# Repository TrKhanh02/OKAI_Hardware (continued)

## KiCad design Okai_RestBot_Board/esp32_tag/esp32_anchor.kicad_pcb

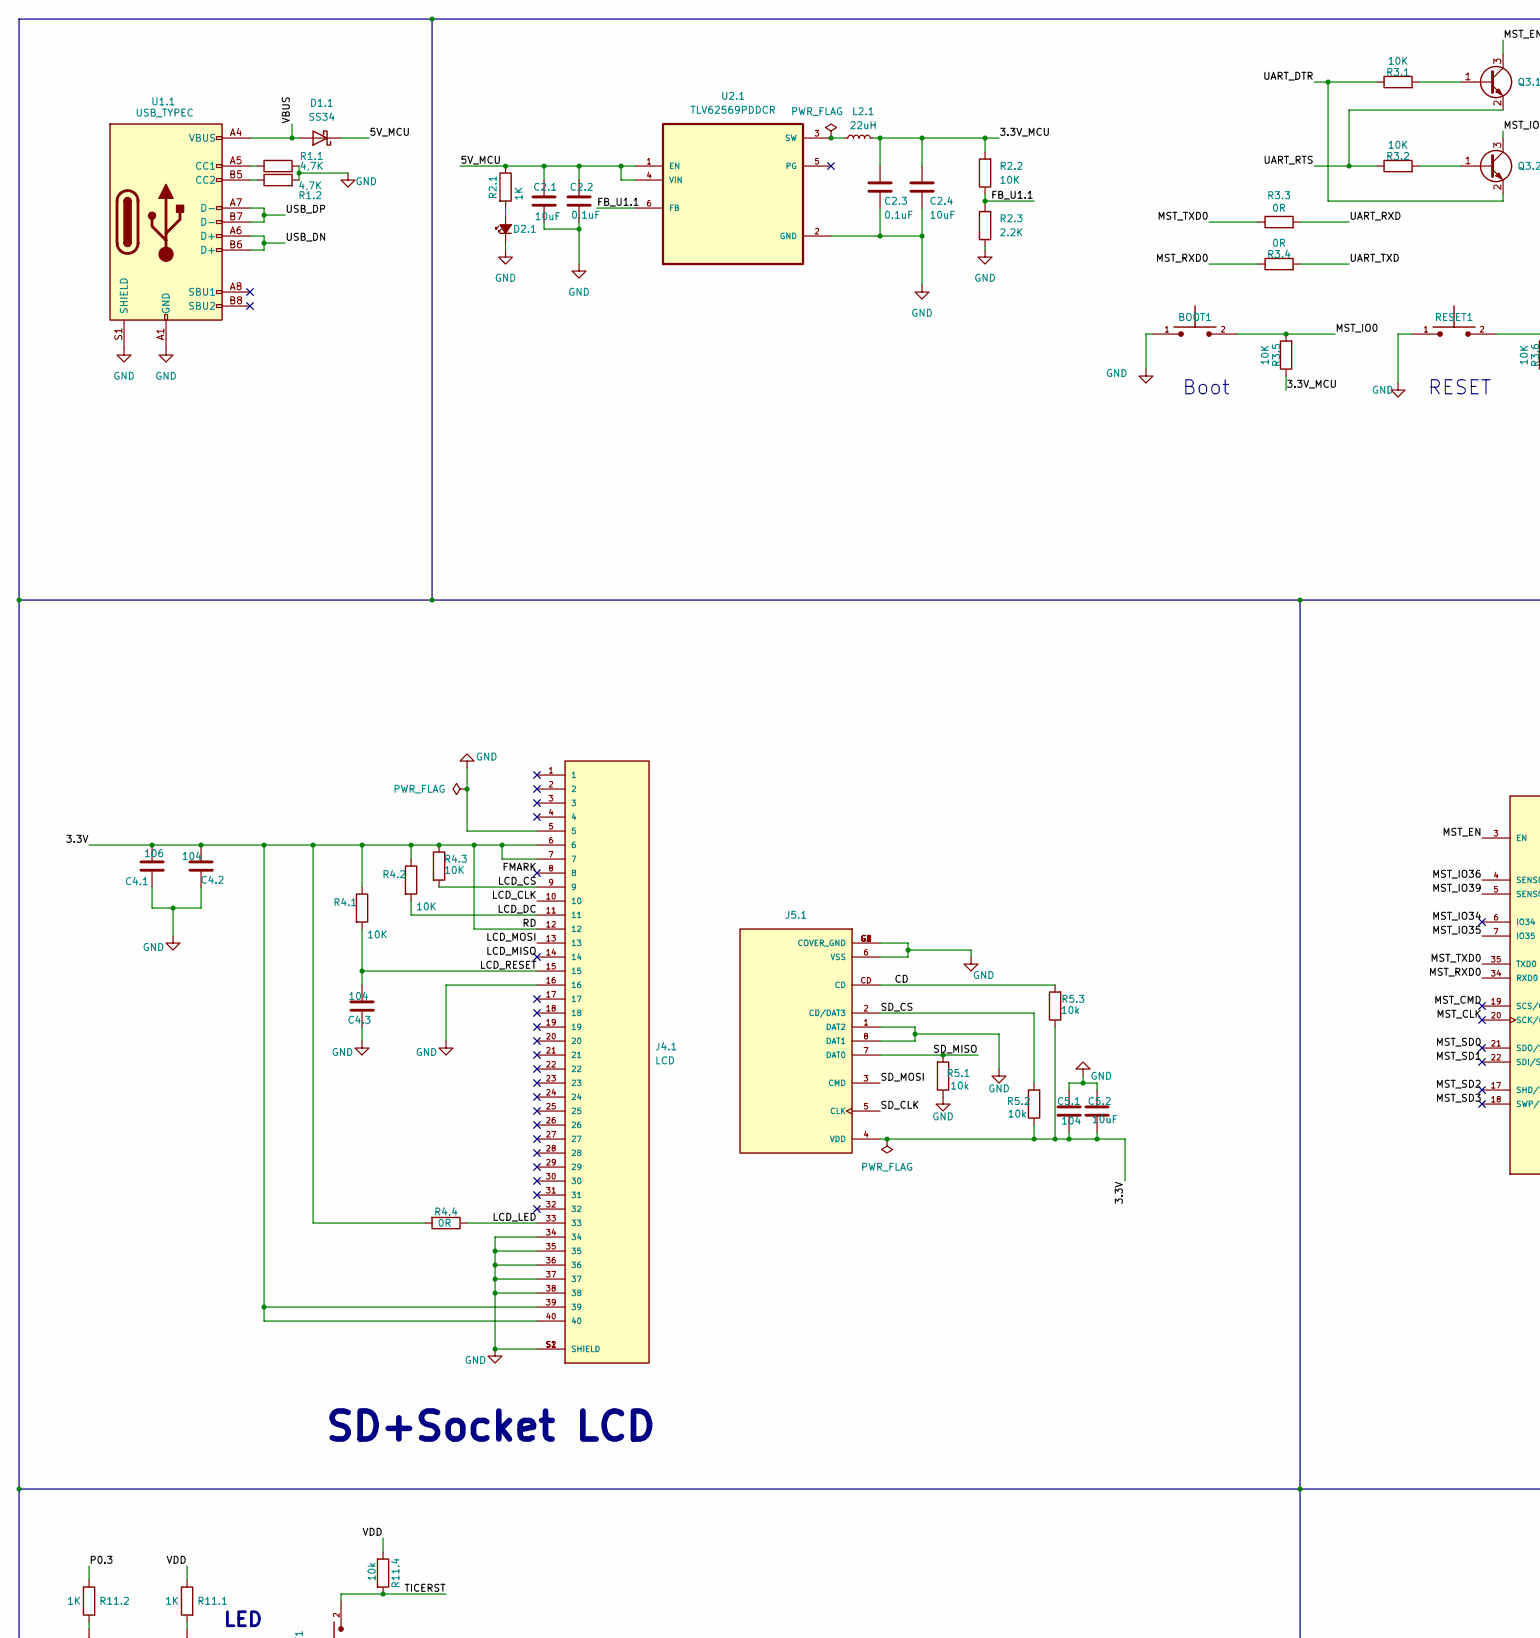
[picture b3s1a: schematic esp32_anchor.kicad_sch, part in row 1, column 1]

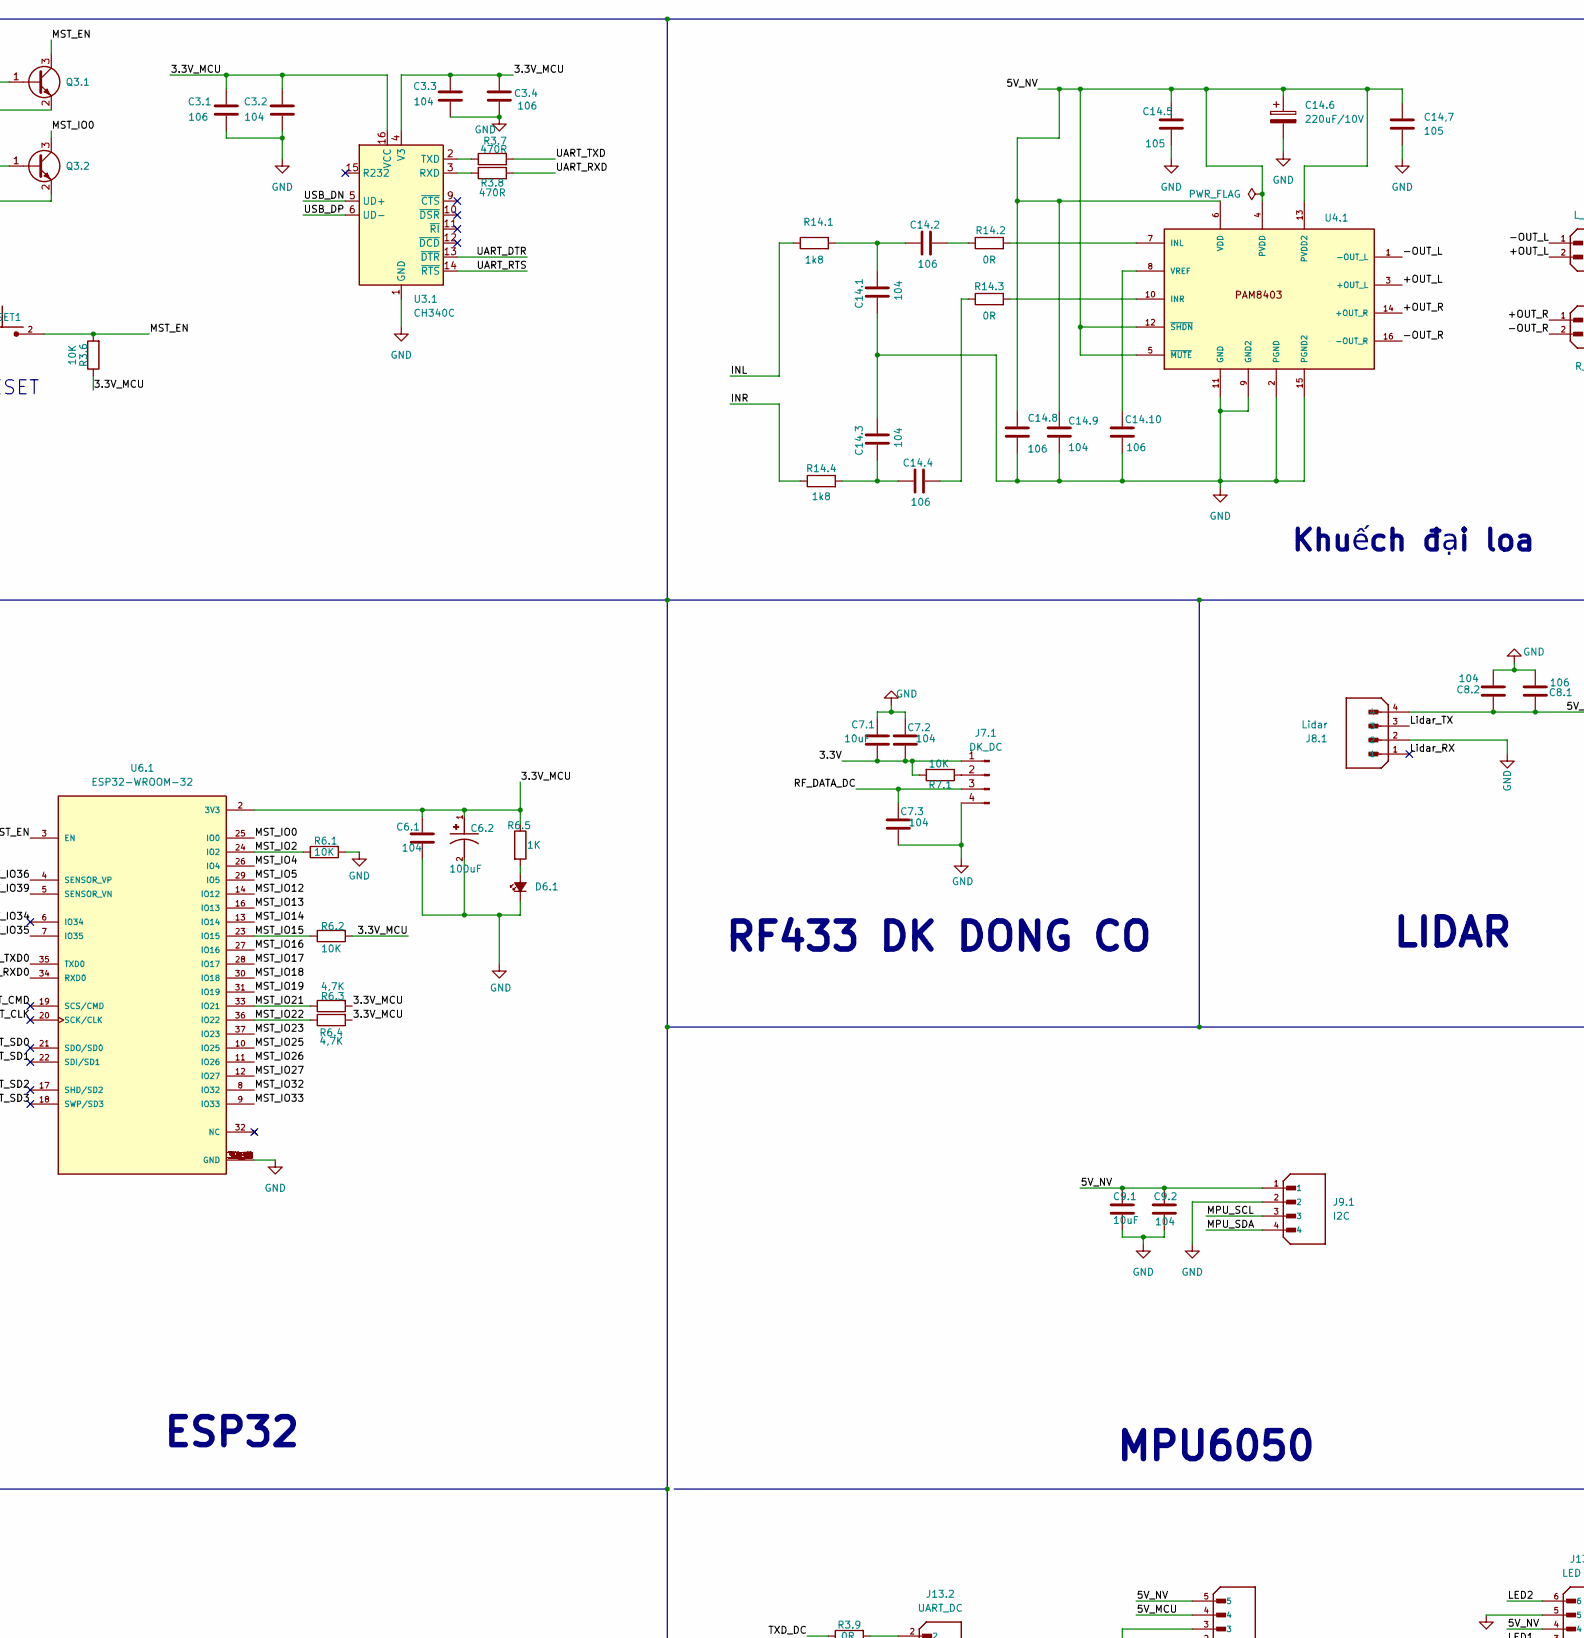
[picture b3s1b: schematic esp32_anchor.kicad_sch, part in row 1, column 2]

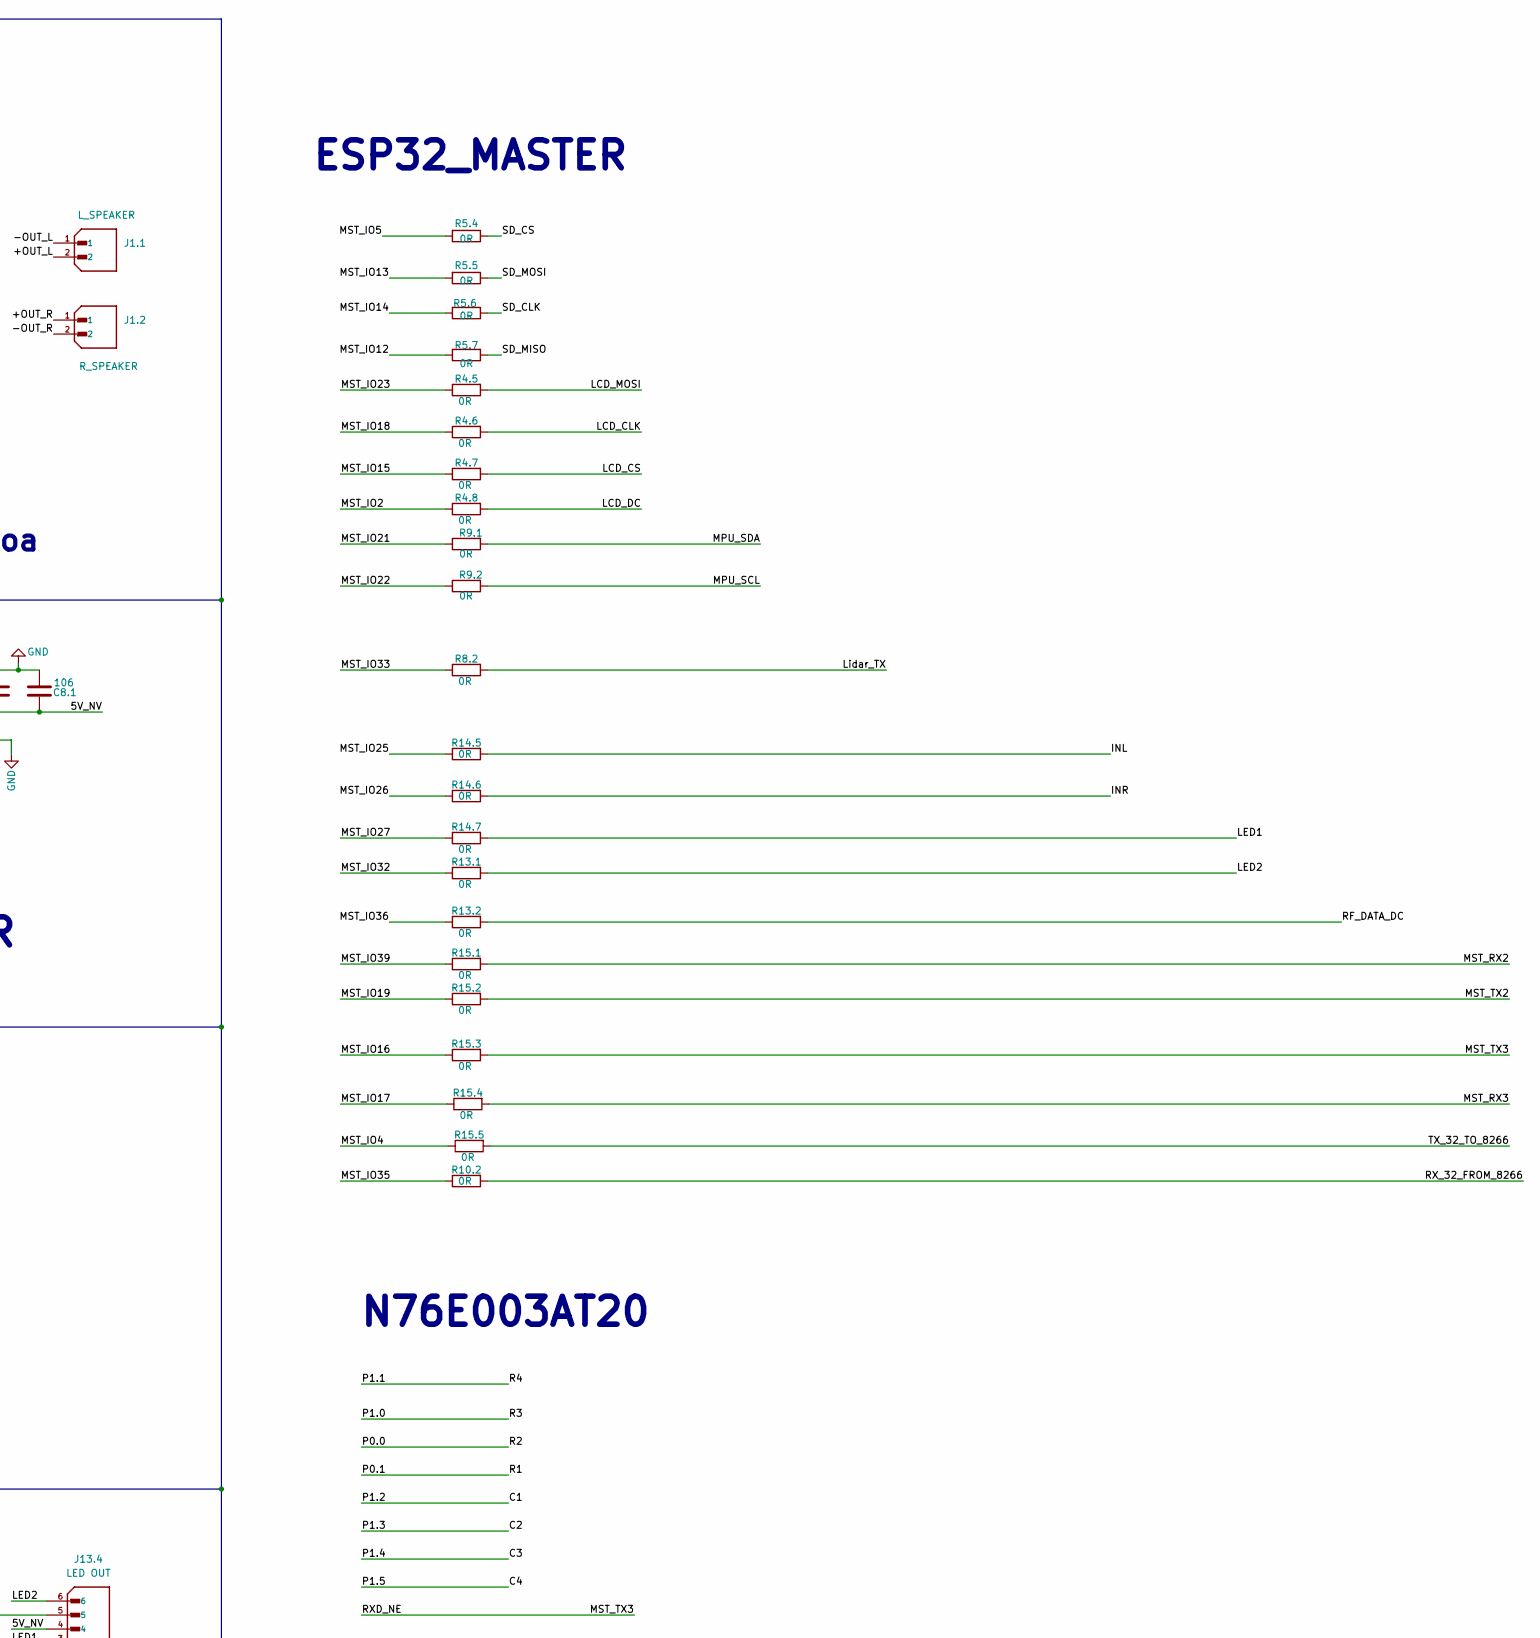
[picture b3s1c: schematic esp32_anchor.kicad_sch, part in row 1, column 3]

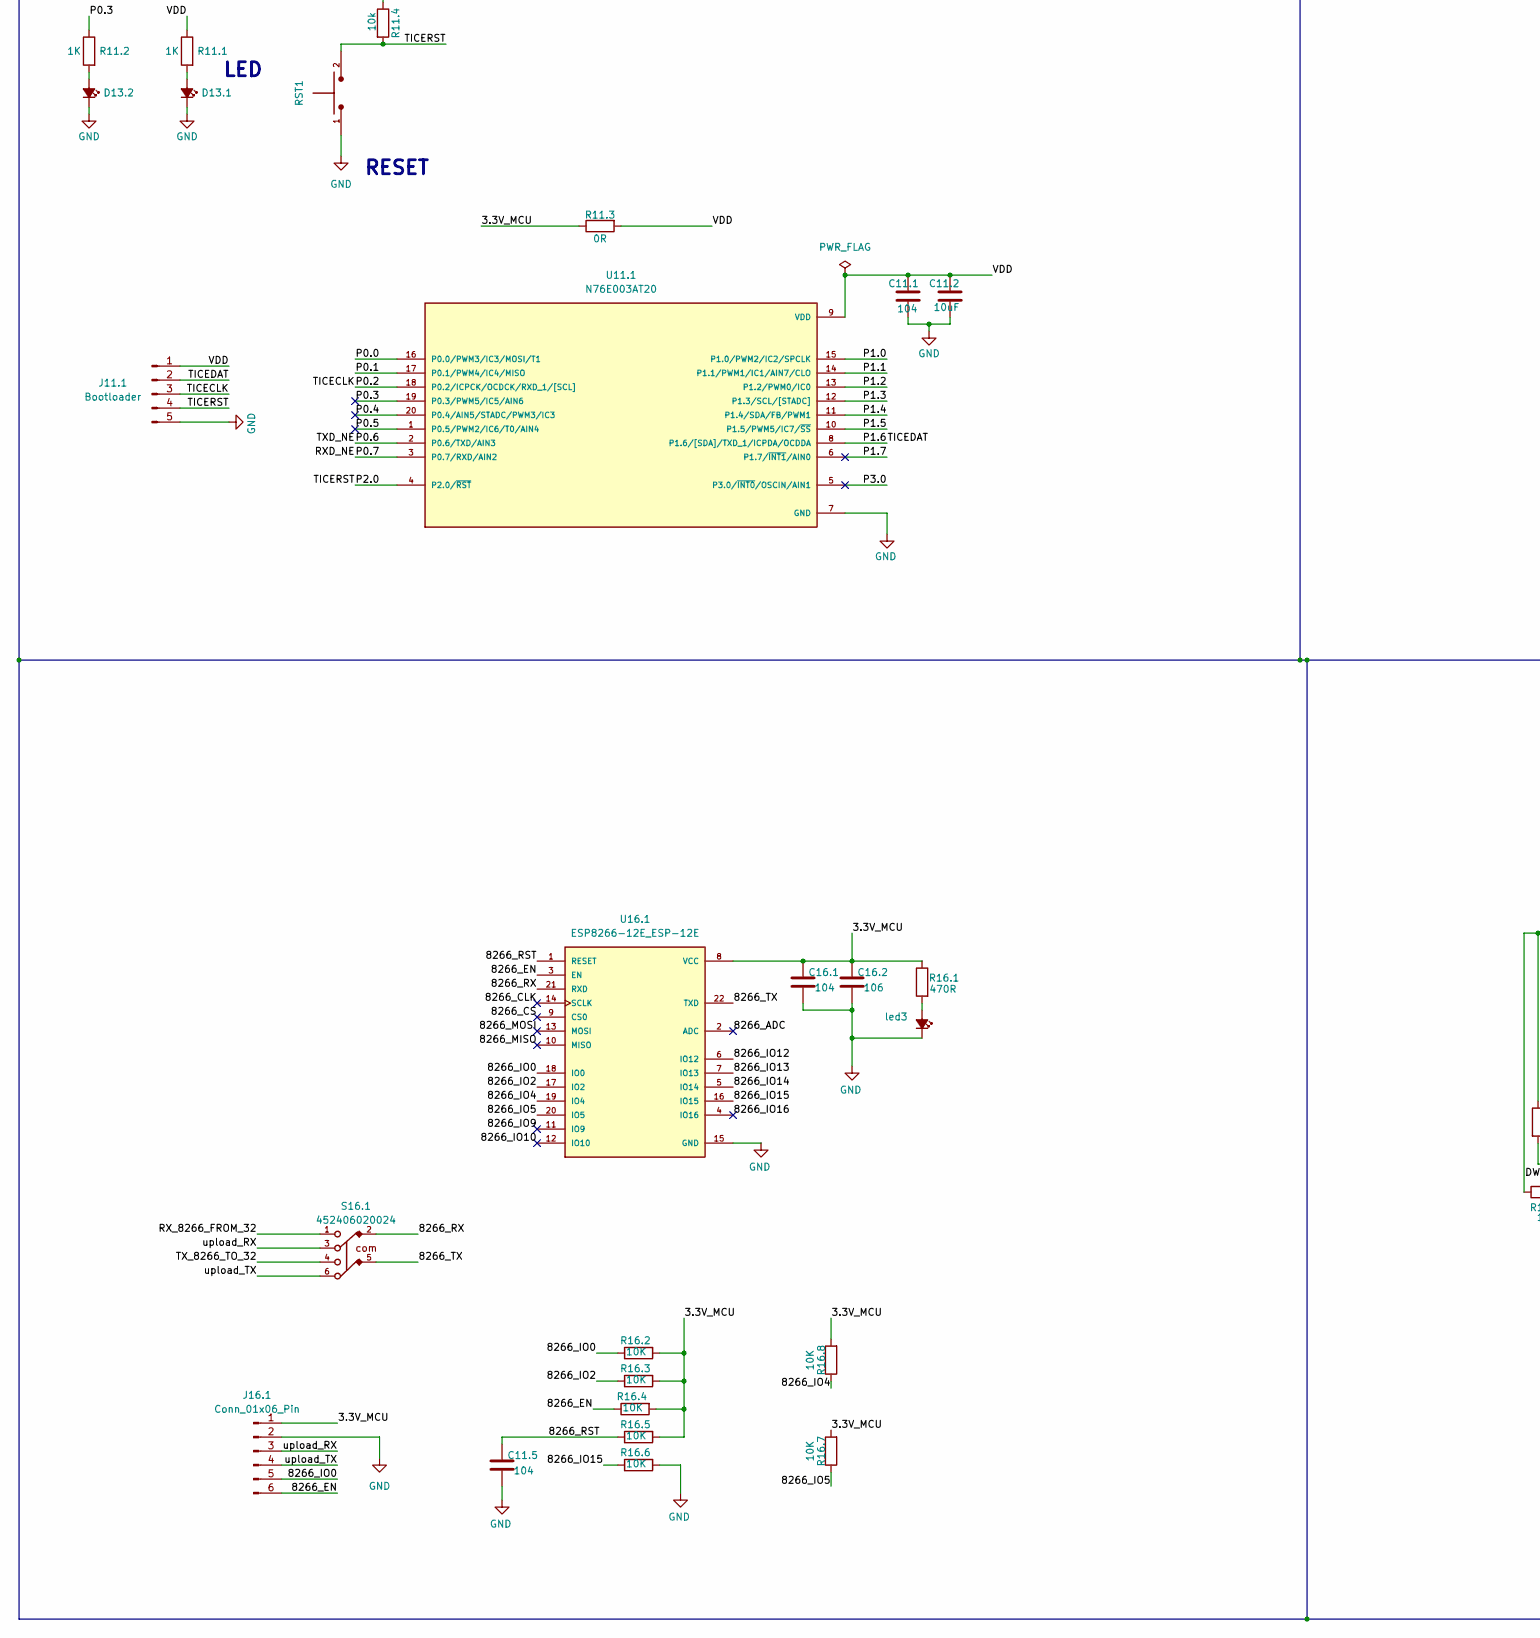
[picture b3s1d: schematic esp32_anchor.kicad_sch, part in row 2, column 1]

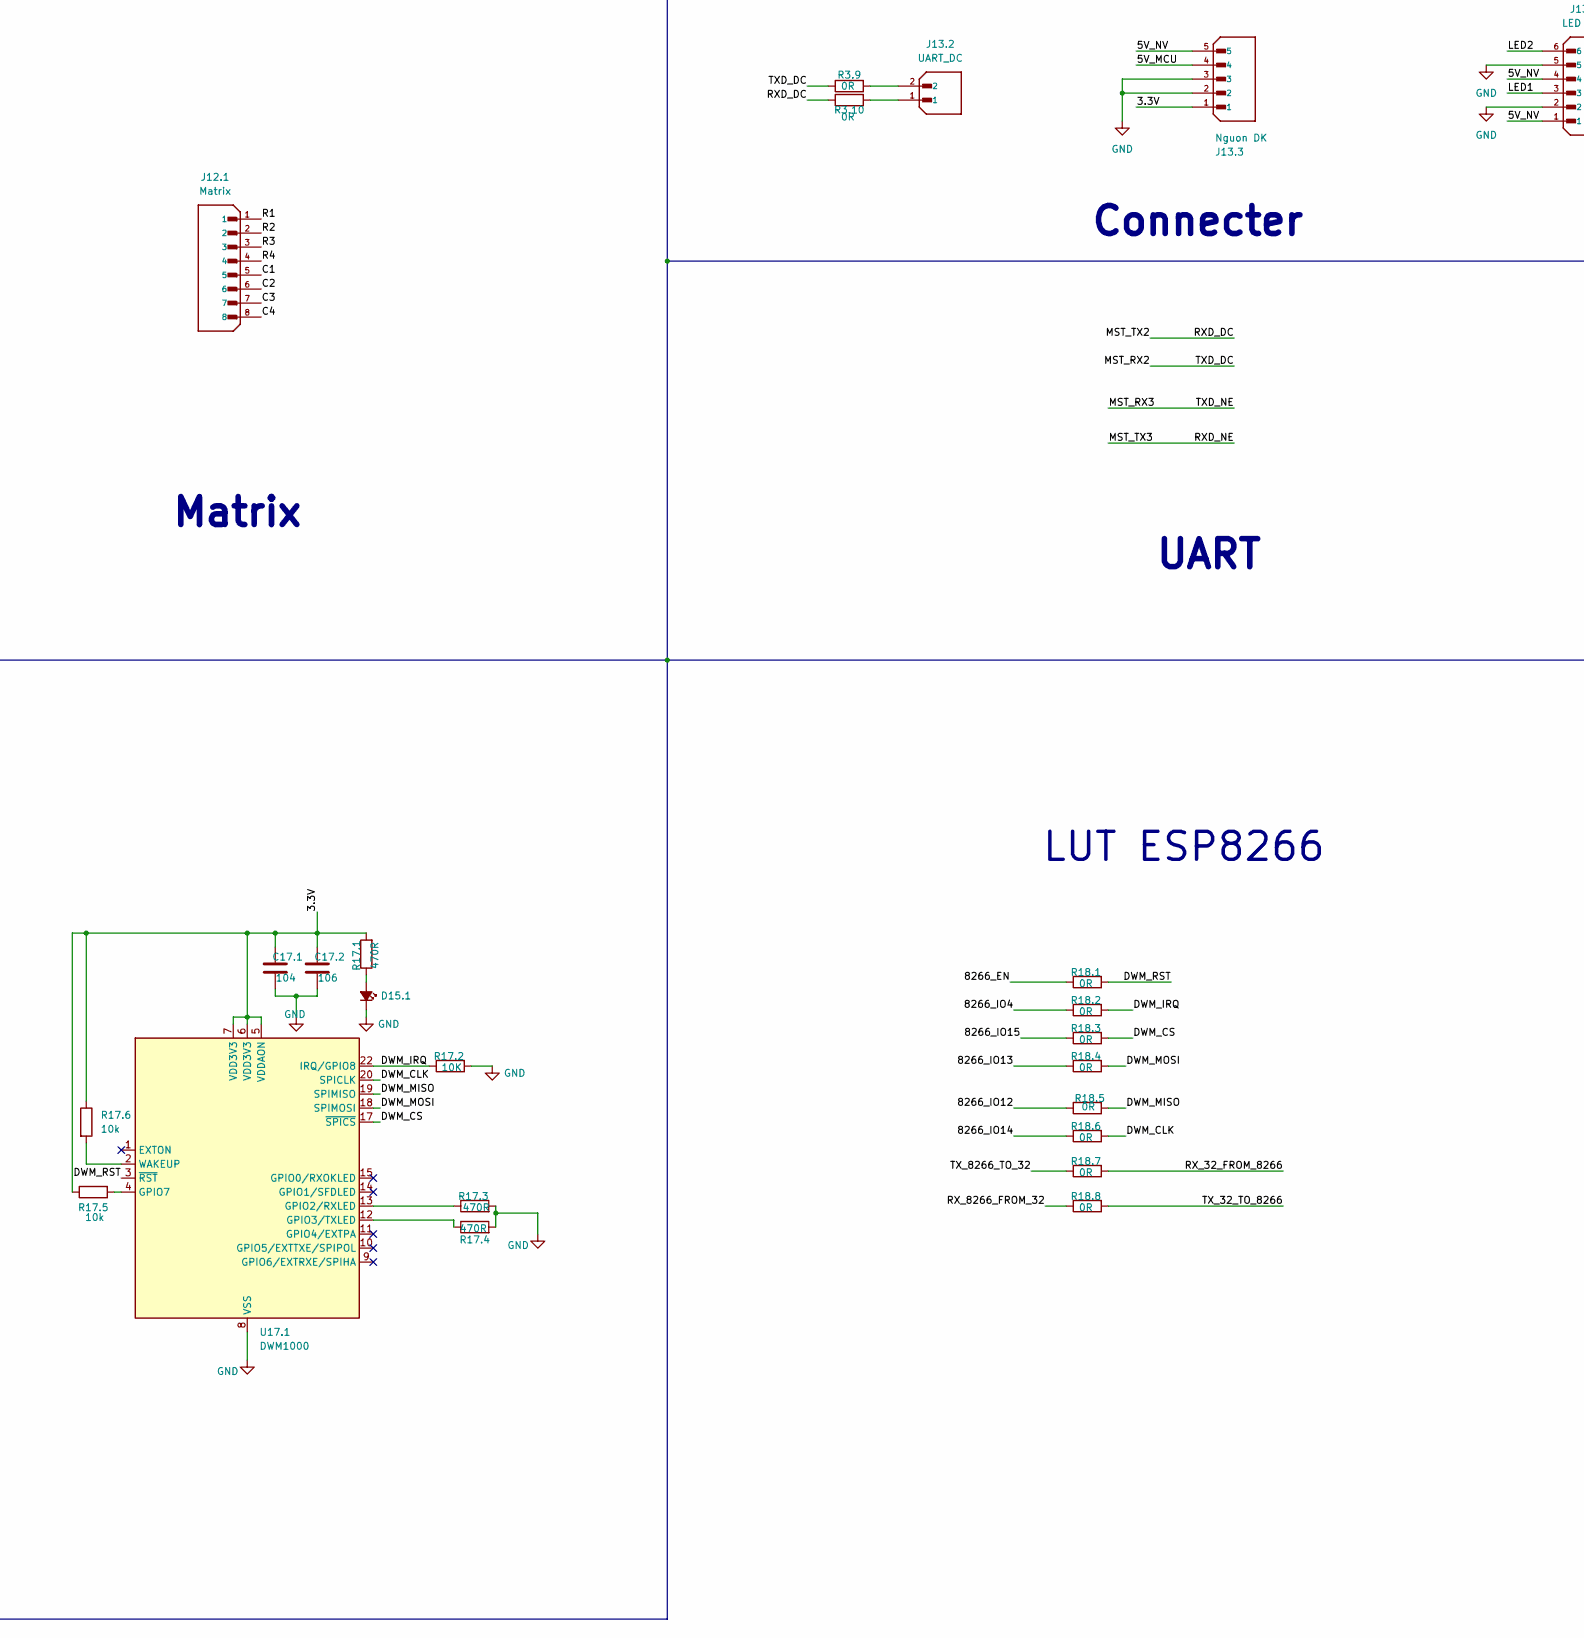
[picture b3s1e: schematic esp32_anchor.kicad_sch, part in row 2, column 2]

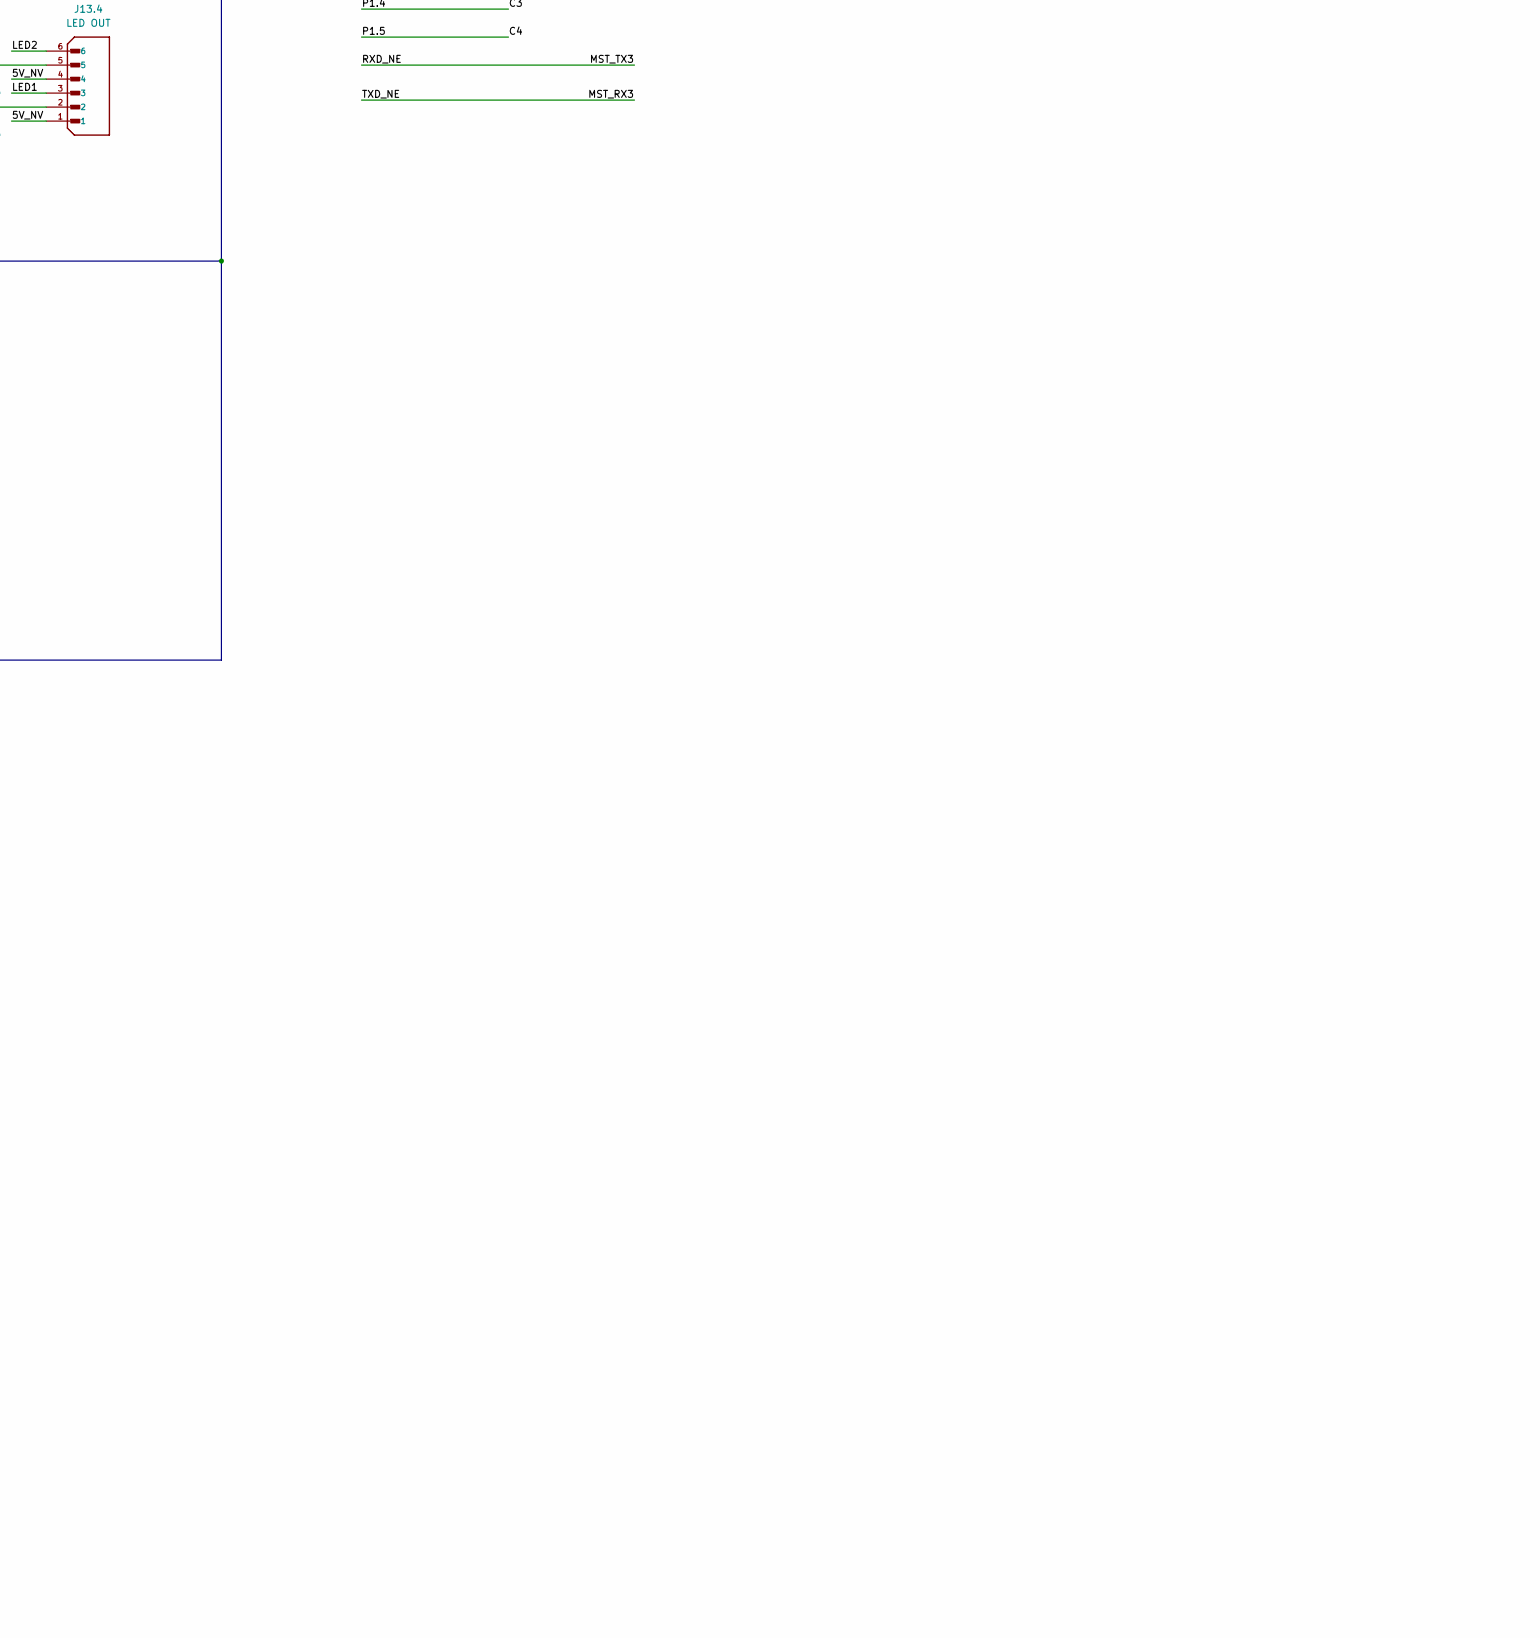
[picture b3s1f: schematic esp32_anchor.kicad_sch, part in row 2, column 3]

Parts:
BOOT1: TS10-63-26-BE-250-SMT-TR; SW_TS10-63-26-BE-250-SMT-TR; PARTREV 1.0
C2.1, C2.4: 10uF; C_0805_2012Metric
C2.2, C2.3: 0.1uF; C_0805_2012Metric
C3.1, C3.4, C4.1, C8.1, C16.2, C17.2: 106; C_0805_2012Metric_Pad1.18x1.45mm_HandSolder
C3.2, C3.3, C4.2, C4.3, C5.1, C6.1, C7.2, C7.3, C8.2, C9.2, C11.1, C11.5, C16.1, C17.1: 104; C_0805_2012Metric_Pad1.18x1.45mm_HandSolder
C5.2, C7.1, C9.1, C11.2: 10uF; C_0805_2012Metric_Pad1.18x1.45mm_HandSolder
C6.2: 100uF; CAPMP3216X180N; PARTREV 031320
C14,7, C14.5: 105; C_0805_2012Metric
C14.1, C14.3, C14.9: 104; C_0805_2012Metric
C14.2, C14.4, C14.8, C14.10: 106; C_0805_2012Metric
C14.6: 220uF/10V; CP_Elec_6.3x5.4
D1.1: SS34; D_SMA
D2.1, D6.1, D13.1, D13.2, D15.1: LED_Small_Filled; LED_0805_2012Metric_Pad1.15x1.40mm_HandSolder
J1.1: L_SPEAKER; JST_B2B-XH-A; PARTREV N/A
J1.2: R_SPEAKER; JST_B2B-XH-A; PARTREV N/A
J4.1: LCD; TE_4-1734592-0; PARTREV C
J5.1: SD; CUI_MSD-1-A; PARTREV 1.0
J7.1: DK_DC; PinSocket_1x04_P2.54mm_Vertical
J8.1: Lidar; HRS_DF14-4P-1.25H_22_
J9.1: I2C; JST_B4B-XH-A_LF__SN_; PARTREV 7/4/21
J11.1: Bootloader; PinHeader_1x05_P2.54mm_Vertical
J12.1: Matrix; JST_B8B-XH-A_LF__SN_; PARTREV 7/4/21
J13.2: UART_DC; JST_B2B-XH-A_LF__SN_; PARTREV N/A
J13.3: Nguon DK; JST_B5B-XH-A; PARTREV 7/4/21
J13.4: LED OUT; JST_B6B-XH-A_LF__SN_; PARTREV 7/4/21
J16.1: Conn_01x06_Pin; PinSocket_1x06_P2.54mm_Vertical
L2.1: 22uH; L_Ferrocore_DLG-0705
Q3.1, Q3.2: SS8050; SOT-23
R1.1, R1.2, R6.3, R6.4: 4,7K; R_0805_2012Metric_Pad1.20x1.40mm_HandSolder
R2.1, R6.5, R11.1, R11.2: 1K; R_0805_2012Metric_Pad1.20x1.40mm_HandSolder
R2.2: 10K; R_0805_2012Metric
R2.3: 2.2K; R_0805_2012Metric
R3.1, R3.2, R3.5, R3.6, R4.1, R4.2, R4.3, R6.1, R6.2, R7.1, R16.2, R16.3, R16.4, R16.5, R16.6, R16.7, R16.8, R17.2: 10K; R_0805_2012Metric_Pad1.20x1.40mm_HandSolder
R3.3, R3.4, R3.9, R3.10, R4.4, R4.5, R4.6, R4.7, R4.8, R5.4, R5.5, R5.6, R5.7, R8.2, R9.1, R9.2, R10.2, R11.3, R13.1, R13.2, R14.5, R14.6, R14.7, R15.1, R15.2, R15.3, R15.4, R15.5, R18.1, R18.2, R18.3, R18.4, R18.5, R18.6, R18.7, R18.8: 0R; R_0805_2012Metric_Pad1.20x1.40mm_HandSolder
R3.7, R3.8, R16.1, R17.1, R17.3, R17.4: 470R; R_0805_2012Metric_Pad1.20x1.40mm_HandSolder
R5.1, R5.2, R5.3, R11.4, R17.5, R17.6: 10k; R_0805_2012Metric_Pad1.20x1.40mm_HandSolder
R14.1, R14.4: 1k8; R_0805_2012Metric
R14.2, R14.3: 0R; R_0805_2012Metric
RESET1: TS10-63-26-BE-250-SMT-TR; SW_TS10-63-26-BE-250-SMT-TR; PARTREV 1.0
RST1: TS10-63-26-BE-250-SMT-TR; SW_TS10-63-26-BE-250-SMT-TR; PARTREV 1.0
S16.1: 452406020024
U1.1: USB_TYPEC; USB_C_Receptacle_HRO_TYPE-C-31-M-12
U2.1: TLV62569PDDCR; SOT95P280X110-6N
U3.1: CH340C; SOIC-16_3.9x9.9mm_P1.27mm
U4.1: PAM8403; SOP-16
U6.1: ESP32-WROOM-32; MODULE_ESP32-WROOM-32
U11.1: N76E003AT20; SOP65P640X120-20N; PARTREV 1.04
U16.1: ESP8266-12E_ESP-12E; XCVR_ESP8266-12E_ESP-12E
U17.1: DWM1000
led3: LED_Small_Filled; LED_0805_2012Metric_Pad1.15x1.40mm_HandSolder

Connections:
/3.3V: C4.1.2, C4.2.2, C5.1.1, C5.2.1, C7.1.2, C7.2.2, C17.1.1, C17.2.1, J4.1.6, J4.1.7, J4.1.12, J4.1.39, J4.1.40, J5.1.4 (VDD), J7.1.1, J13.3.1, R4.1.1, R4.2.1, R4.3.1, R4.4.2, R5.2.1, R5.3.1, R7.1.2, R17.1.2, R17.5.1, R17.6.1, U17.1.5 (VDDAON), U17.1.6 (VDD3V3), U17.1.7 (VDD3V3)
/3.3V_MCU: C2.3.1, C2.4.1, C3.1.2, C3.2.2, C3.3.2, C3.4.2, C6.1.1, C6.2.1, C16.1.1, C16.2.1, J16.1.1, L2.1.1, R2.2.2, R3.5.1, R3.6.1, R6.2.2, R6.3.2, R6.4.2, R6.5.1, R11.3.1, R16.1.1, R16.2.2, R16.3.2, R16.4.2, R16.5.2, R16.7.2, R16.8.2, U3.1.4 (V3), U3.1.16 (VCC), U6.1.2 (3V3), U16.1.8 (VCC)
/5V_MCU: C2.1.1, C2.2.1, D1.1.1 (K), J13.3.4, R2.1.1, U2.1.1 (EN), U2.1.4 (VIN)
/5V_NV: C8.1.1, C8.2.1, C9.1.1, C9.2.1, C14,7.2, C14.5.2, C14.6.1, C14.8.2, C14.9.2, J8.1.4, J9.1.1, J13.3.5, J13.4.1, J13.4.4, U4.1.4 (PVDD), U4.1.5 (~MUTE), U4.1.6 (VDD), U4.1.12 (~SHDN), U4.1.13 (PVDD2)
/8266_ADC: U16.1.2 (ADC)
/8266_CLK: U16.1.14 (SCLK)
/8266_CS: U16.1.9 (CS0)
/8266_EN: J16.1.6, R16.4.1, R18.1.1, U16.1.3 (EN)
/8266_IO0: J16.1.5, R16.2.1, U16.1.18 (IO0)
/8266_IO2: R16.3.1, U16.1.17 (IO2)
/8266_IO4: R16.8.1, R18.2.1, U16.1.19 (IO4)
/8266_IO5: R16.7.1, U16.1.20 (IO5)
/8266_IO9: U16.1.11 (IO9)
/8266_IO10: U16.1.12 (IO10)
/8266_IO12: R18.5.1, U16.1.6 (IO12)
/8266_IO13: R18.4.1, U16.1.7 (IO13)
/8266_IO14: R18.6.1, U16.1.5 (IO14)
/8266_IO15: R16.6.1, R18.3.1, U16.1.16 (IO15)
/8266_IO16: U16.1.4 (IO16)
/8266_MISO: U16.1.10 (MISO)
/8266_MOSI: U16.1.13 (MOSI)
/8266_RST: C11.5.1, R16.5.1, U16.1.1 (RESET)
/8266_RX: S16.1.2, U16.1.21 (RXD)
/8266_TX: S16.1.5, U16.1.22 (TXD)
/+OUT_L: J1.1.2, U4.1.3 (+OUT_L)
/+OUT_R: J1.2.1, U4.1.14 (+OUT_R)
/-OUT_L: J1.1.1, U4.1.1 (-OUT_L)
/-OUT_R: J1.2.2, U4.1.16 (-OUT_R)
/C1: J12.1.5, U11.1.13 (P1.2/PWM0/IC0)
/C2: J12.1.6, U11.1.12 (P1.3/SCL/[STADC])
/C3: J12.1.7, U11.1.11 (P1.4/SDA/FB/PWM1)
/C4: J12.1.8, U11.1.10 (P1.5/PWM5/IC7/~SS)
/CD: J5.1.CD, R5.3.2
/DWM_CLK: R18.6.2, U17.1.20 (SPICLK)
/DWM_CS: R18.3.2, U17.1.17 (~SPICS)
/DWM_IRQ: R17.2.1, R18.2.2, U17.1.22 (IRQ/GPIO8)
/DWM_MISO: R18.5.2, U17.1.19 (SPIMISO)
/DWM_MOSI: R18.4.2, U17.1.18 (SPIMOSI)
/DWM_RST: R18.1.2, U17.1.3 (~RST)
/FB_U1.1: R2.2.1, R2.3.2, U2.1.6 (FB)
/FMARK: J4.1.8
/INL: R14.1.1, R14.5.2
/INR: R14.4.1, R14.6.2
/LCD_CLK: J4.1.10, R4.6.2
/LCD_CS: J4.1.9, R4.3.2, R4.7.2
/LCD_DC: J4.1.11, R4.2.2, R4.8.2
/LCD_LED: J4.1.33, R4.4.1
/LCD_MISO: J4.1.14
/LCD_MOSI: J4.1.13, R4.5.2
/LCD_RESET: C4.3.2, J4.1.15, R4.1.2
/LED1: J13.4.3, R14.7.2
/LED2: J13.4.6, R13.1.2
/Lidar_RX: J8.1.1
/Lidar_TX: J8.1.3, R8.2.2
/MPU_SCL: J9.1.3, R9.2.2
/MPU_SDA: J9.1.4, R9.1.2
/MST_CLK: U6.1.20 (SCK/CLK)
/MST_CMD: U6.1.19 (SCS/CMD)
/MST_EN: Q3.1.3 (C), R3.6.2, RESET1.2, U6.1.3 (EN)
/MST_IO0: BOOT1.2, Q3.2.3 (C), R3.5.2, U6.1.25 (IO0)
/MST_IO2: R4.8.1, R6.1.1, U6.1.24 (IO2)
/MST_IO4: R15.5.1, U6.1.26 (IO4)
/MST_IO5: R5.4.2, U6.1.29 (IO5)
/MST_IO12: R5.7.1, U6.1.14 (IO12)
/MST_IO13: R5.5.2, U6.1.16 (IO13)
/MST_IO14: R5.6.2, U6.1.13 (IO14)
/MST_IO15: R4.7.1, R6.2.1, U6.1.23 (IO15)
/MST_IO16: R15.3.1, U6.1.27 (IO16)
/MST_IO17: R15.4.1, U6.1.28 (IO17)
/MST_IO18: R4.6.1, U6.1.30 (IO18)
/MST_IO19: R15.2.1, U6.1.31 (IO19)
/MST_IO21: R6.3.1, R9.1.1, U6.1.33 (IO21)
/MST_IO22: R6.4.1, R9.2.1, U6.1.36 (IO22)
/MST_IO23: R4.5.1, U6.1.37 (IO23)
/MST_IO25: R14.5.1, U6.1.10 (IO25)
/MST_IO26: R14.6.1, U6.1.11 (IO26)
/MST_IO27: R14.7.1, U6.1.12 (IO27)
/MST_IO32: R13.1.1, U6.1.8 (IO32)
/MST_IO33: R8.2.1, U6.1.9 (IO33)
/MST_IO34: U6.1.6 (IO34)
/MST_IO35: R10.2.1, U6.1.7 (IO35)
/MST_IO36: R13.2.1, U6.1.4 (SENSOR_VP)
/MST_IO39: R15.1.1, U6.1.5 (SENSOR_VN)
/MST_RX2: R3.9.1, R15.1.2
/MST_RX3: R15.4.2, U11.1.2 (P0.6/TXD/AIN3)
/MST_RXD0: R3.4.1, U6.1.34 (RXD0)
/MST_SD0: U6.1.21 (SDO/SD0)
/MST_SD1: U6.1.22 (SDI/SD1)
/MST_SD2: U6.1.17 (SHD/SD2)
/MST_SD3: U6.1.18 (SWP/SD3)
/MST_TX2: R3.10.1, R15.2.2
/MST_TX3: R15.3.2, U11.1.3 (P0.7/RXD/AIN2)
/MST_TXD0: R3.3.1, U6.1.35 (TXD0)
/P0.0: J12.1.2, U11.1.16 (P0.0/PWM3/IC3/MOSI/T1)
/P0.1: J12.1.1, U11.1.17 (P0.1/PWM4/IC4/MISO)
/P0.2: J11.1.3, U11.1.18 (P0.2/ICPCK/OCDCK/RXD_1/[SCL])
/P0.3: R11.2.1, U11.1.19 (P0.3/PWM5/IC5/AIN6)
/P0.4: U11.1.20 (P0.4/AIN5/STADC/PWM3/IC3)
/P0.5: U11.1.1 (P0.5/PWM2/IC6/T0/AIN4)
/P1.0: J12.1.3, U11.1.15 (P1.0/PWM2/IC2/SPCLK)
/P1.1: J12.1.4, U11.1.14 (P1.1/PWM1/IC1/AIN7/CLO)
/P1.6: J11.1.2, U11.1.8 (P1.6/[SDA]/TXD_1/ICPDA/OCDDA)
/P1.7: U11.1.6 (P1.7/~INT1/AIN0)
/P2.0: J11.1.4, R11.4.2, RST1.2, U11.1.4 (P2.0/~RST)
/P3.0: U11.1.5 (P3.0/~INT0/OSCIN/AIN1)
/RF_DATA_DC: C7.3.1, J7.1.3, R13.2.2
/RX_32_FROM_8266: R10.2.2, R18.7.2
/RX_8266_FROM_32: R18.8.1, S16.1.1
/SD_CLK: J5.1.5 (CLK), R5.6.1
/SD_CS: J5.1.2 (CD/DAT3), R5.2.2, R5.4.1
/SD_MISO: J5.1.7 (DAT0), R5.1.2, R5.7.2
/SD_MOSI: J5.1.3 (CMD), R5.5.1
/TX_32_TO_8266: R15.5.2, R18.8.2
/TX_8266_TO_32: R18.7.1, S16.1.4
/UART_DTR: Q3.2.2 (E), R3.1.1, U3.1.13 (~DTR)
/UART_RTS: Q3.1.2 (E), R3.2.1, U3.1.14 (~RTS)
/UART_RXD: R3.3.2, R3.8.2
/UART_TXD: R3.4.2, R3.7.2
/USB_DN: U1.1.A6 (D+), U1.1.B6 (D+), U3.1.5 (UD+)
/USB_DP: U1.1.A7 (D-), U1.1.B7 (D-), U3.1.6 (UD-)
/VBUS: D1.1.2 (A), U1.1.A4 (VBUS), U1.1.A9 (VBUS), U1.1.B4 (VBUS), U1.1.B9 (VBUS)
/VDD: C11.1.1, C11.2.1, J11.1.1, R11.1.1, R11.3.2, R11.4.1, U11.1.9 (VDD)
/upload_RX: J16.1.3, S16.1.3
/upload_TX: J16.1.4, S16.1.6
GND: BOOT1.1, C2.1.2, C2.2.2, C2.3.2, C2.4.2, C3.1.1, C3.2.1, C3.3.1, C3.4.1, C4.1.1, C4.2.1, C4.3.1, C5.1.2, C5.2.2, C6.1.2, C6.2.2, C7.1.1, C7.2.1, C7.3.2, C8.1.2, C8.2.2, C9.1.2, C9.2.2, C11.1.2, C11.2.2, C11.5.2, C14,7.1, C14.1.2, C14.3.1, C14.5.1, C14.6.2, C14.8.1, C14.9.1, C14.10.1, C16.1.2, C16.2.2, C17.1.2, C17.2.2, D2.1.1 (K), D6.1.1 (K), D13.1.1 (K), D13.2.1 (K), D15.1.1 (K), J4.1.5, J4.1.16, J4.1.34, J4.1.35, J4.1.36, J4.1.37, J4.1.38, J4.1.S1 (SHIELD), J4.1.S2 (SHIELD), J5.1.1 (DAT2), J5.1.6 (VSS), J5.1.8 (DAT1), J5.1.G1 (COVER_GND), J5.1.G2 (COVER_GND), J5.1.G3 (COVER_GND), J5.1.G4 (COVER_GND), J7.1.4, J8.1.2, J9.1.2, J11.1.5, J13.3.2, J13.3.3, J13.4.2, J13.4.5, J16.1.2, R1.1.2, R1.2.2, R2.3.1, R5.1.1, R6.1.2, R16.6.2, R17.2.2, R17.3.2, R17.4.2, RESET1.1, RST1.1, U1.1.A1 (GND), U1.1.A12 (GND), U1.1.B1 (GND), U1.1.B12 (GND), U1.1.S1 (SHIELD), U2.1.2 (GND), U3.1.1 (GND), U4.1.2 (PGND), U4.1.9 (GND2), U4.1.11 (GND), U4.1.15 (PGND2), U6.1.1 (GND), U6.1.15 (GND), U6.1.38 (GND), U6.1.39_1 (GND), U6.1.39_2 (GND), U6.1.39_3 (GND), U6.1.39_4 (GND), U6.1.39_5 (GND), U6.1.39_6 (GND), U6.1.39_7 (GND), U6.1.39_8 (GND), U6.1.39_9 (GND), U6.1.39_10 (GND), U6.1.39_11 (GND), U6.1.39_12 (GND), U6.1.39_13 (GND), U6.1.39_14 (GND), U6.1.39_15 (GND)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
unnamed: C14.1.1, C14.2.2, R14.1.2
unnamed: C14.2.1, R14.2.1
unnamed: C14.3.2, C14.4.2, R14.4.2
unnamed: C14.4.1, R14.3.1
unnamed: D2.1.2 (A), R2.1.2
unnamed: D6.1.2 (A), R6.5.2
unnamed: D13.1.2 (A), R11.1.2
unnamed: D13.2.2 (A), R11.2.2
unnamed: D15.1.2 (A), R17.1.1
unnamed: J7.1.2, R7.1.1
unnamed: J13.2.1, R3.10.2
unnamed: J13.2.2, R3.9.2
unnamed: Q3.1.1 (B), R3.1.2
unnamed: Q3.2.1 (B), R3.2.2
unnamed: R1.1.1, U1.1.A5 (CC1)
unnamed: R1.2.1, U1.1.B5 (CC2)
unnamed: L2.1.2, U2.1.3 (SW)
unnamed: R3.8.1, U3.1.3 (RXD)
unnamed: R3.7.1, U3.1.2 (TXD)
unnamed: R14.2.2, U4.1.7 (INL)
unnamed: R14.3.2, U4.1.10 (INR)
unnamed: C14.10.2, U4.1.8 (VREF)
unnamed: R17.3.1, U17.1.13 (GPIO2/RXLED)
unnamed: R17.4.1, U17.1.12 (GPIO3/TXLED)
unnamed: R17.5.2, U17.1.4 (GPIO7)
unnamed: R17.6.2, U17.1.2 (WAKEUP)
unnamed: R16.1.2, led3.2 (A)

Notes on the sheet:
Connecter
RESET
ESP32
LIDAR
LUT ESP8266
Khuếch đại loa
SD+Socket LCD
N76E003AT20
LED
ESP32_MASTER
RF433 DK DONG CO
UART
MPU6050
Boot
Matrix

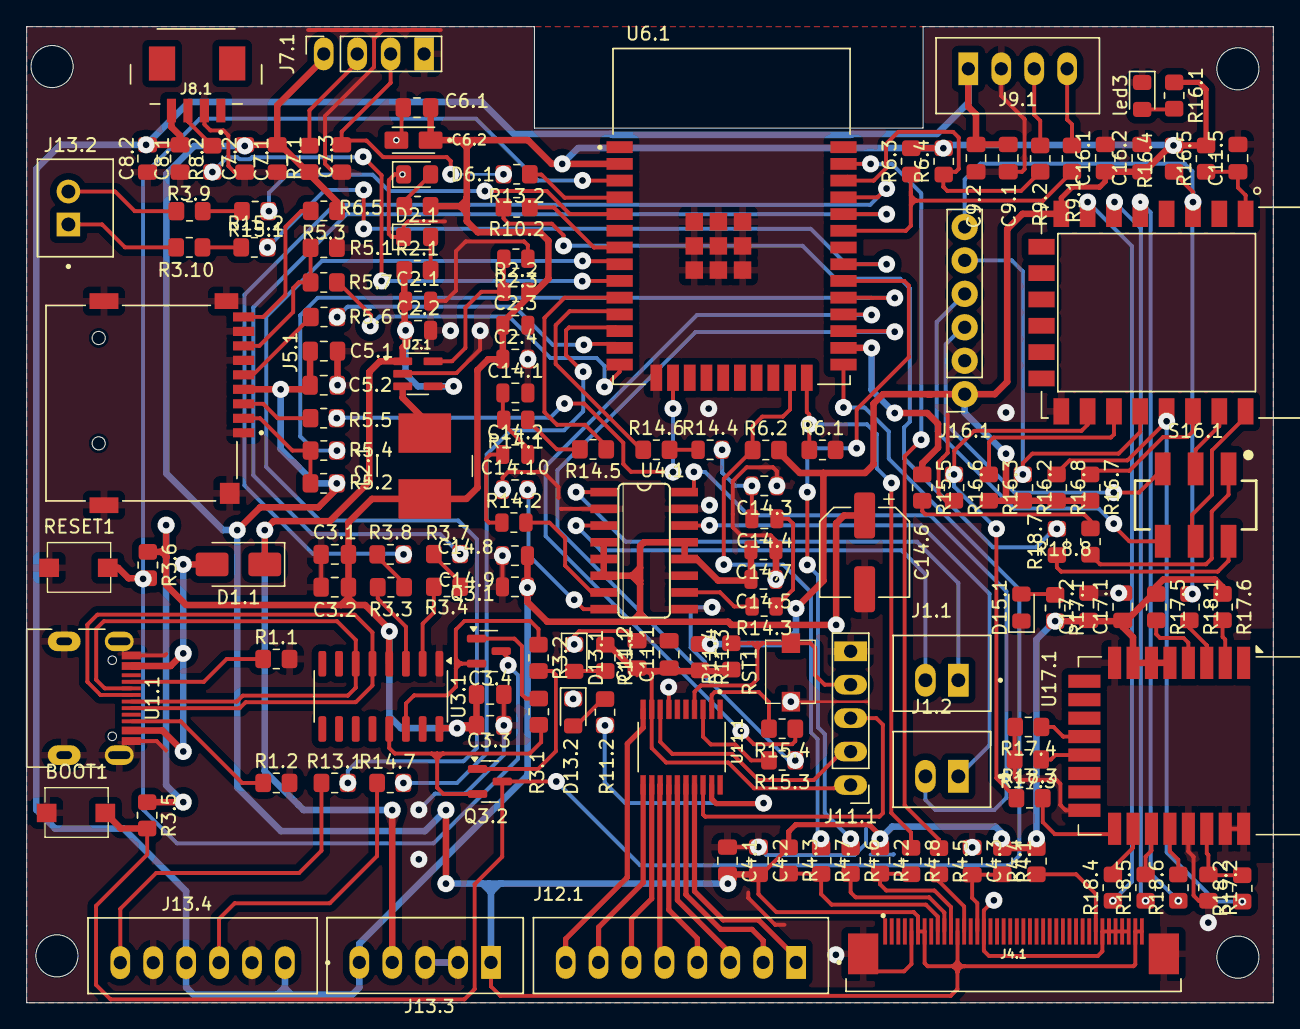
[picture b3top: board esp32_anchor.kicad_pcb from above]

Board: 2 copper layers, 94.7 x 74.1 mm, 154 parts (0 on the bottom side), 130 nets.
